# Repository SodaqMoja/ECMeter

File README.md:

ECMeter
=======

This repository includes all open source files related to the EC-Meter
that I have developed for _M2M4ALL_, the company I work for.  This
circuit board includes an analog frontend to measure the electrical
conductivity and temperature of water. The board will have to be cast
in resin with the probes sticking out in order to submerge the board
for long durations.

This is the Arduino library required to use the EC Meter easily. The
hardware files are also included.

##Documentation
We've added Doxygen so that the documentation can be generated from
the source code.

##Examples

#####demo
Reads the onboard temperature sensor, system voltage, resistance,
conductivity and prints the value every two seconds.

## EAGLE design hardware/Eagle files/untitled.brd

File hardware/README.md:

#Hardware

_BOM.xlsx_ includes the build-of-materials for this project including Farnell links. If you are sourcing the components from another website, please make sure the resistors are 1% thin-film or better. The analog circuitry has very fine tolerances.

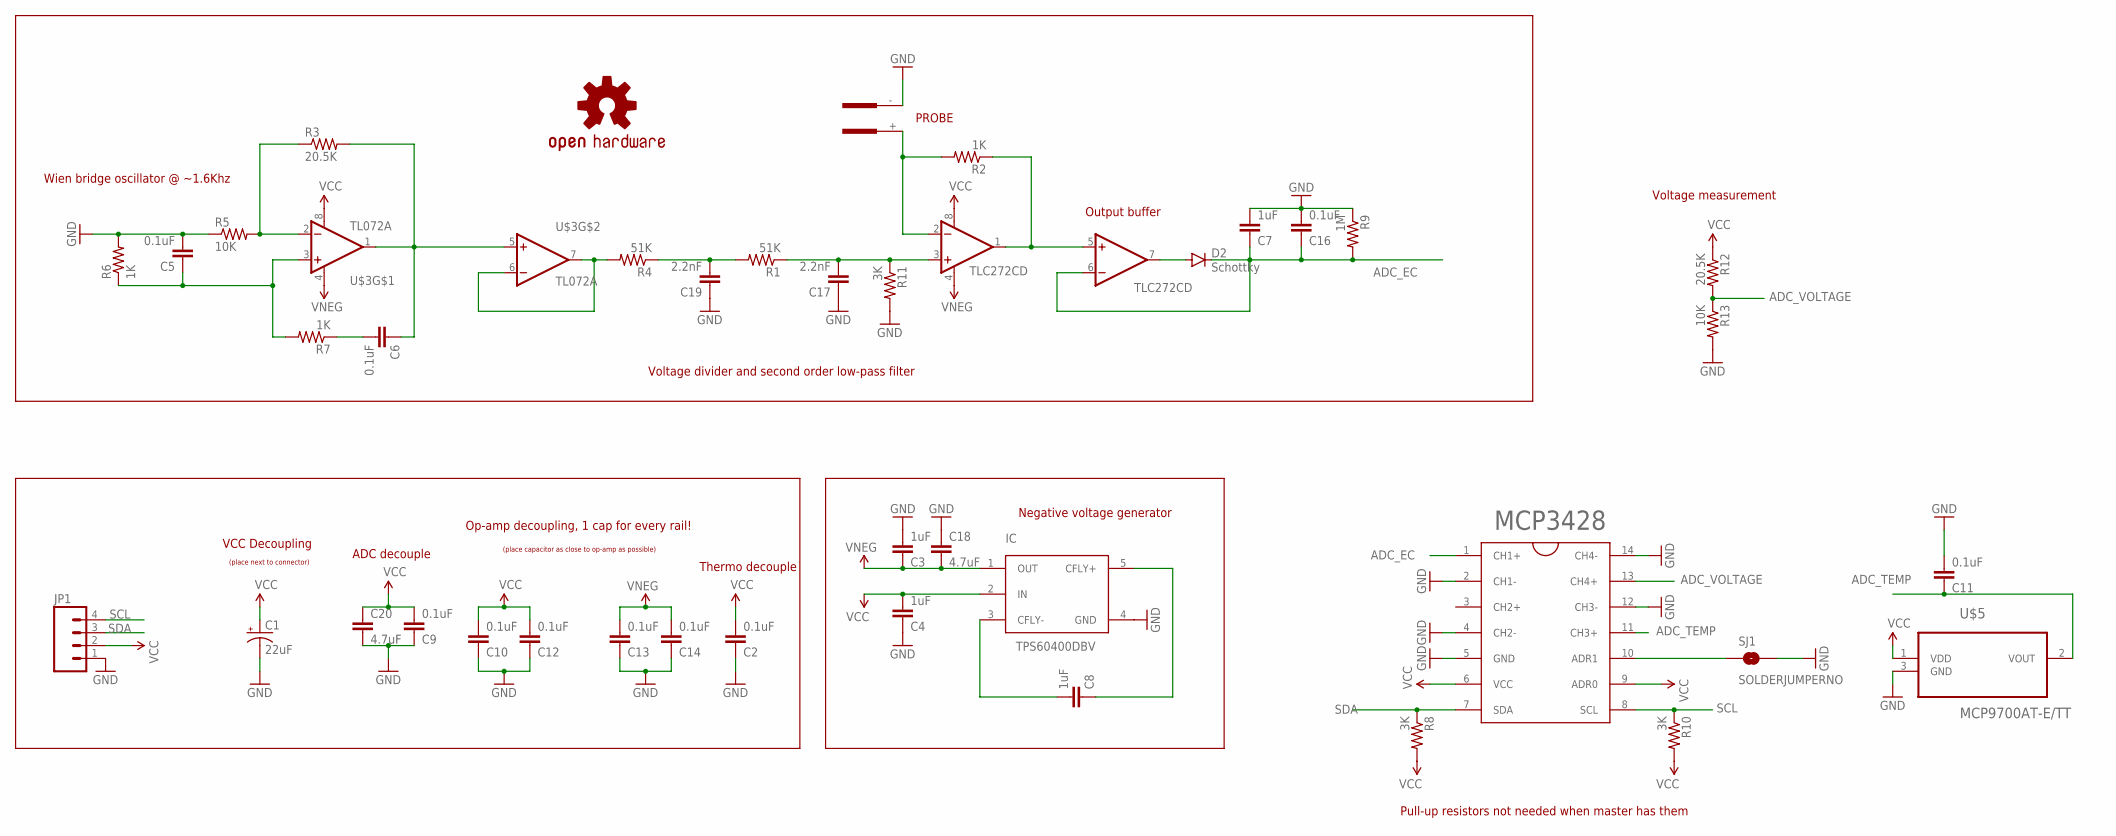
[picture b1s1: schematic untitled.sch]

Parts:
C1: 22uF; EIA3216
C2, C5, C6, C9, C10, C11, C12, C13, C14, C16: 0.1uF; 0603-CAP
C3, C4, C7, C8: 1uF; 0603-CAP
C17, C19: 2.2nF; 0603-CAP
C18, C20: 4.7uF; 0805
D2: Schottky; SOD-323
IC: TPS60400DBV; SOT23-5
JP1: M04LONGPADS; 1X04_LONGPADS
LOGO1: OSHW-LOGOM; OSHW-LOGO-M
MCP3428: MCP3428; SO14
R1, R4: 51K; 0603-RES
R2, R6, R7: 1K; 0603-RES
R3, R12: 20.5K; 0603-RES
R5, R13: 10K; 0603-RES
R8, R10, R11: 3K; 0603-RES
R9: 1M; 0603-RES
SJ1: SOLDERJUMPERNO; SJ_2S-NO
U$1: TLC272CD; SOIC8
U$2: K1-PROBE
U$3: TL072A; SOIC8
U$5: MCP9700AT-E/TT; SOT95P237X112-3N

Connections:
ADC_EC: C7.1, C16.1, D2.C, MCP3428.1 (CH1+), R9.2, U$1.6 (-IN)
ADC_TEMP: C11.1, MCP3428.11 (CH3+), U$5.2 (VOUT)
ADC_VOLTAGE: MCP3428.13 (CH4+), R12.2, R13.1
GND: C1.C (-), C2.1, C3.2, C4.1, C5.2, C7.2, C9.1, C10.1, C11.2, C12.1, C13.1, C14.1, C16.2, C17.1, C18.1, C19.1, C20.2, IC.4 (GND), JP1.1, MCP3428.2 (CH1-), MCP3428.4 (CH2-), MCP3428.5 (GND), MCP3428.12 (CH3-), MCP3428.14 (CH4-), R5.1, R6.2, R9.1, R11.2, R13.2, SJ1.2, U$2.-, U$5.3 (GND)
unnamed: C6.1, R3.2, U$3.1 (OUT), U$3.5 (+IN)
unnamed: R3.1, R5.2, U$3.2 (-IN)
unnamed: C5.1, R6.1, R7.2, U$3.3 (+IN)
unnamed: C6.2, R7.1
unnamed: R4.2, U$3.6 (-IN), U$3.7 (OUT)
unnamed: C17.2, R1.1, R11.1, U$1.3 (+IN)
unnamed: R2.1, U$1.1 (OUT), U$1.5 (+IN)
unnamed: R2.2, U$1.2 (-IN), U$2.+
unnamed: D2.A, U$1.7 (OUT)
unnamed: C8.1, IC.5 (CFLY+)
unnamed: C8.2, IC.3 (CFLY-)
unnamed: C19.2, R1.2, R4.1
unnamed: MCP3428.10 (ADR1), SJ1.1
SCL: JP1.4, MCP3428.8 (SCL), R10.1
SDA: JP1.3, MCP3428.7 (SDA), R8.1
VCC: C1.A (+), C2.2, C4.2, C9.2, C10.2, C12.2, C20.1, IC.2 (IN), JP1.2, MCP3428.6 (VCC), MCP3428.9 (ADR0), R8.2, R10.2, R12.1, U$1.8 (V+), U$3.8 (V+), U$5.1 (VDD)
VNEG: C3.1, C13.2, C14.2, C18.2, IC.1 (OUT), U$1.4 (V-), U$3.4 (V-)

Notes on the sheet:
VCC Decoupling
Wien bridge oscillator @ ~1.6Khz
Output buffer
Op-amp decoupling, 1 cap for every rail!
(place capacitor as close to op-amp as possible)
(place next to connector)
Negative voltage generator
PROBE
ADC decouple
Thermo decouple
Voltage divider and second order low-pass filter
Voltage measurement
Pull-up resistors not needed when master has them

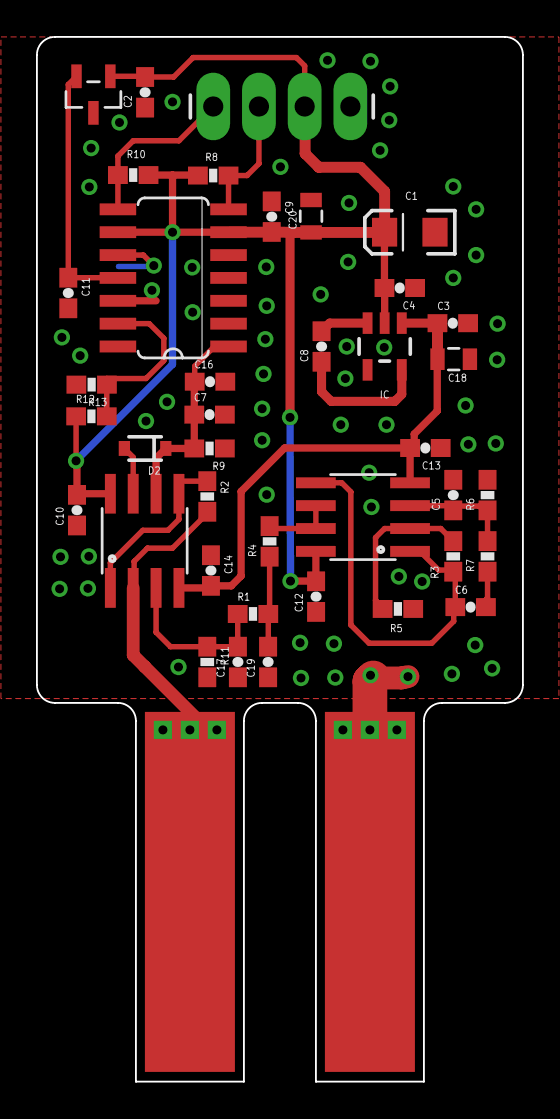
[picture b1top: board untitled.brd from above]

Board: 2 copper layers, 27.0 x 58.0 mm, 42 parts (1 on the bottom side), 21 nets.

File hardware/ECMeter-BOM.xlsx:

Qty | Value | Device | Package | Farnell
10 | 0.1uF | CAPACITOR | 0603 | x
4 | 1uF | CAPACITOR | 0603 | 1759399
3 | 1K | 1% 0603 RESISTOR | 0603 | 2325213
3 | 3K | 1% 0603 RESISTOR | 0603 | 2059357
2 | 10K | 1% 0603 RESISTOR | 0603 | 2325241
2 | 2.2nF | CAPACITOR | 0603 | 1658866
2 | 4.7uF | CAPACITOR | 0805 | 1759420
2 | 51K | 1% 0603 RESISTOR | 0603 | 9331310
1 | 22uF | CAPACITOR | 3216 | 2333013
1 | 1M | 1% 0603 RESISTOR | 0603 | 9330410
2 | 20.5K | 1% 0603 RESISTOR | 0603 | 1527616
1 | MCP3428 | MCP3428 | SO14 | 1825014
1 | MCP9700AT | MCP9700AT-E/TT | SOT23-3 | 1605577
1 | Schottky | DIODESOD | SOD-323 | 1907691
2 | TL072A | TL072A | SOIC8 | 9593322
1 | TPS60400DBV | TPS60400DBV | SOT23-5 | 8457751

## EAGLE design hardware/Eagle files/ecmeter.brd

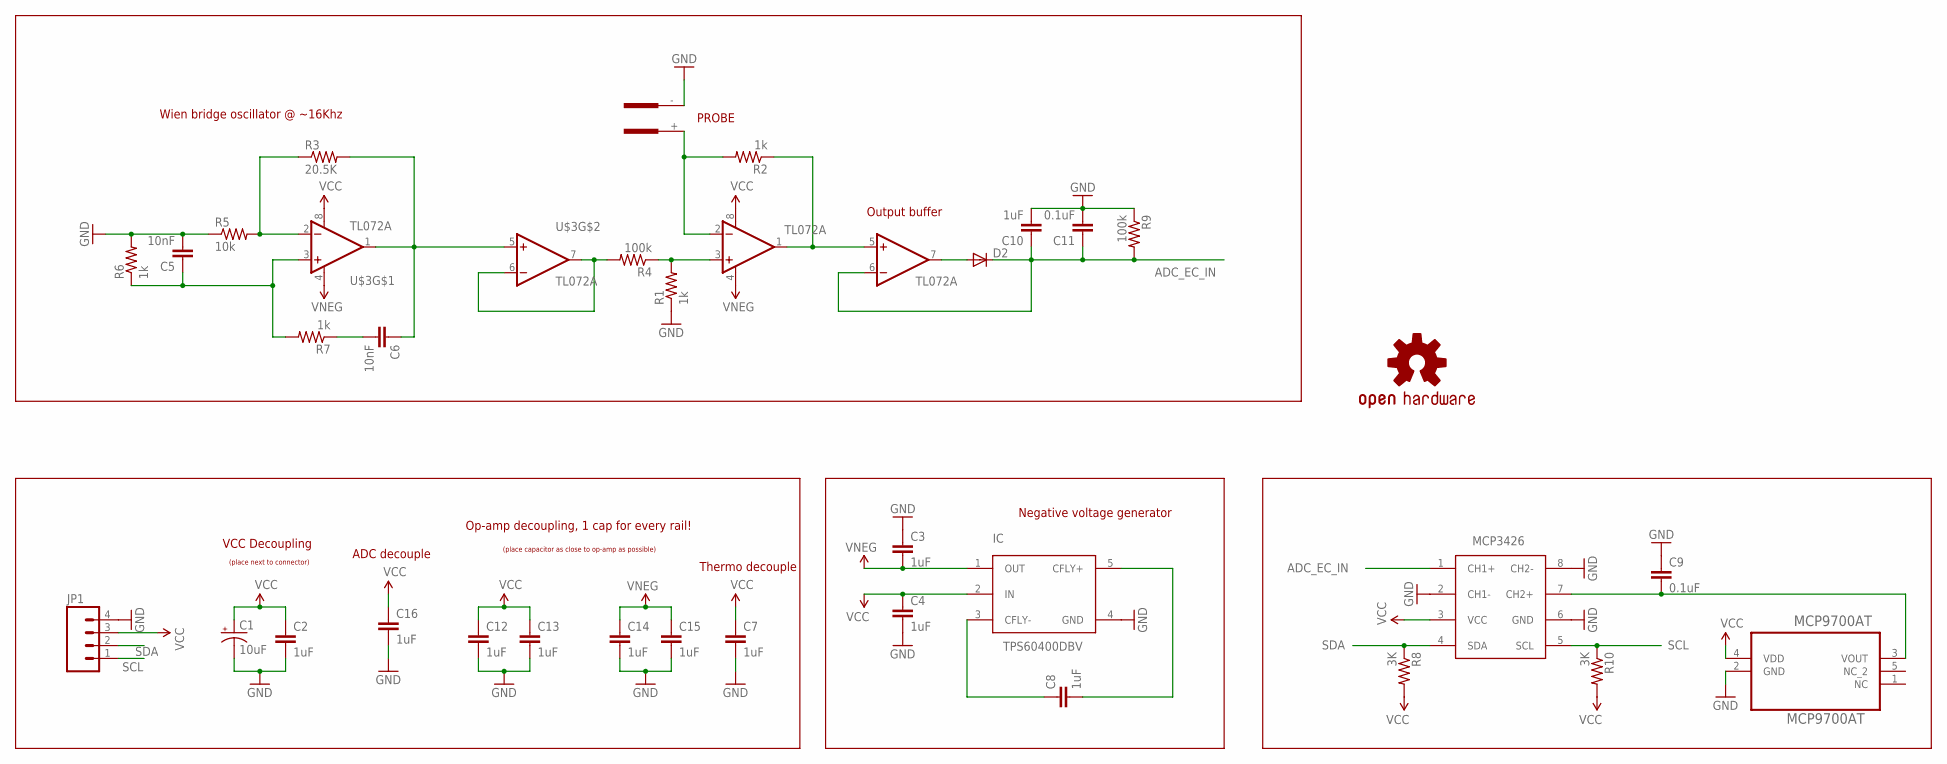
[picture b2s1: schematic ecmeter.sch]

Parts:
C1: 10uF; EIA3216
C2, C3, C4, C7, C8, C10, C12, C13, C14, C15, C16: 1uF; 0805
C5, C6: 10nF; 0603-CAP
C9, C11: 0.1uF; 0805
D2: DIODESOD; SOD-323
IC: TPS60400DBV; SOT23-5
JP1: M04POLAR; MOLEX-1X4
LOGO1: OSHW-LOGOM; OSHW-LOGO-M
MCP9700AT: MCP9700AT; SOT65P210X110-5N
R1, R2, R6, R7: 1k; 0603-RES
R3: 20.5K; 0603-RES
R4, R9: 100k; 0603-RES
R5: 10k; 0603-RES
R8, R10: 3K; 0603-RES
U$1, U$3: TL072A; SOIC8
U$2: K1-PROBE
U$4: MCP3426; SOIC8

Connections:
ADC_EC_IN: C10.1, C11.1, D2.1 (C), R9.2, U$1.6 (-IN), U$4.1 (CH1+)
GND: C1.C (-), C2.2, C3.1, C4.2, C5.2, C7.2, C9.1, C10.2, C11.2, C12.2, C13.2, C14.2, C15.2, C16.2, IC.4 (GND), JP1.4, MCP9700AT.2 (GND), R1.1, R5.1, R6.2, R9.1, U$2.-, U$4.2 (CH1-), U$4.6 (GND), U$4.8 (CH2-)
unnamed: C6.1, R3.2, U$3.1 (OUT), U$3.5 (+IN)
unnamed: R3.1, R5.2, U$3.2 (-IN)
unnamed: C5.1, R6.1, R7.2, U$3.3 (+IN)
unnamed: C6.2, R7.1
unnamed: R4.2, U$3.6 (-IN), U$3.7 (OUT)
unnamed: R1.2, R4.1, U$1.3 (+IN)
unnamed: R2.1, U$1.1 (OUT), U$1.5 (+IN)
unnamed: R2.2, U$1.2 (-IN), U$2.+
unnamed: D2.2 (A), U$1.7 (OUT)
unnamed: C8.2, IC.5 (CFLY+)
unnamed: C8.1, IC.3 (CFLY-)
unnamed: C9.2, MCP9700AT.3 (VOUT), U$4.7 (CH2+)
SCL: JP1.1, R10.1, U$4.5 (SCL)
SDA: JP1.2, R8.1, U$4.4 (SDA)
VCC: C1.A (+), C2.1, C4.1, C7.1, C12.1, C13.1, C16.1, IC.2 (IN), JP1.3, MCP9700AT.4 (VDD), R8.2, R10.2, U$1.8 (V+), U$3.8 (V+), U$4.3 (VCC)
VNEG: C3.2, C14.1, C15.1, IC.1 (OUT), U$1.4 (V-), U$3.4 (V-)

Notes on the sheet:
VCC Decoupling
Wien bridge oscillator @ ~16Khz
Output buffer
Op-amp decoupling, 1 cap for every rail!
(place capacitor as close to op-amp as possible)
(place next to connector)
Negative voltage generator
PROBE
ADC decouple
Thermo decouple

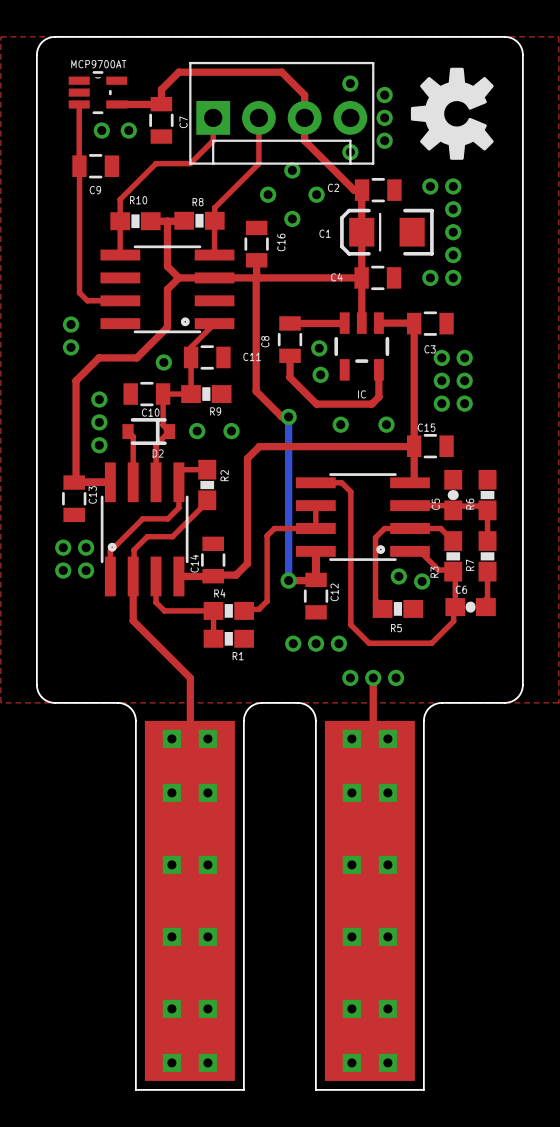
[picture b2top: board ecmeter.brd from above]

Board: 2 copper layers, 27.0 x 58.5 mm, 35 parts (0 on the bottom side), 18 nets.

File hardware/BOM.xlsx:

Qty | Qty * 10 | Value | Device | Package | Farnell |  | Legend:
1 | 10 | Schottky | DIODESOD | SOD-323 | 1907691 |  | SILICON
2 | 20 | 100k | RESISTOR | 0603-RES | 1527690 |  | RESISTOR
1 | 10 | 10k | RESISTOR | 0603-RES | 1527581 |  | IC
1 | 10 | 10uF | TANTALUM CAP | EIA3216 | 2333009 |  | CAPACITOR
1 | 10 | 20.5K | RESISTOR | 0603-RES | 1527616
1 | 10 | MCP3426 | MCP3426 ADC | SOIC8 | 1825012
1 | 10 | MCP9700AT | MCP9700AT | SC70 | 1332165
1 | 10 | TPS60400DBV | TPS60400DBV | SOT23-5 | 8457751
2 | 20 | 0.1uF | CAPACITOR | 0805 | 1759166
2 | 20 | 10nF | CAPACITOR | 0603-CAP | 1865545
2 | 20 | 3K | RESISTOR | 0603-RES | 2326512
2 | 20 | TL072A | TL072A | SOIC8 | 9593322
4 | 40 | 1k | RESISTOR | 0603-RES | 2008335
11 | 110 | 1uF | CAPACITOR | 0805 | 9227792

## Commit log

2014-05-25 Added library folder, testing
2014-05-25 Added example to libraries folder
2014-05-26 Added hardware files
2014-09-05 Updates library and added example sketch
2014-10-10 Updated library
    Added way to measure resistance and conductivity
2014-10-24 Reorganize directory structure
2014-10-24 Updated to revision 2
    All files updated to revision 2 of the ECMeter. New code and hardware
    files added.
2014-10-24 Remove reference to SoftI2CMaster in the README
    Also updated the README about the example(s)
2014-11-01 Added conductivity measurement
    Added (calibrated) conductivity measurement. Also added 2 lines of code
    that will reduce the I2C clock speed so long range communication is
    possible.
2014-11-01 Move EC_ADDR macro to ECMeter.cpp
    And also the Wire.h include is moved to ECMeter.cpp
2014-11-07 Testing SourceTree
2014-11-07 Removed text files from sourcetree test
2014-11-07 Create a class ECMeter and all functions class methods
2014-11-07 Make calibrationVal a private constant for ECMeter
2014-11-11 Move all macros (defines) to the .cpp module and make readChannel private
    The header file is now as clean as can be. This is the class interface.
    Nothing more must be accessible for the outside world.
2014-11-11 The channel values are (16 bit) signed
2014-11-11 Split readChannel into a function that reads raw and one that does voltage
2014-11-14 Removed hardware folder, will be added later to a dedicated hardware repository.
2014-11-17 Added <inttypes.h>
2014-11-17 Changed I2C clock speed to 10Khz
2014-11-22 Only white space changes (indent 2, no TAB's)
    We're using indent 2, which is more or less standard for Arduino. Also
    I don't like the use of TAB, unless they represent 8 spaces.
2014-11-22 Use stdint.h instead of inttypes.h because we only need the types
    inttypes.h (despite the name) is used to give all the printf format stuff
    and we don't need that.
2014-11-22 Add .gitignore
2014-11-22 Add first set of doxygen comments
2014-11-22 Add LGPL
2014-11-22 More comments converted to doxygen style
2014-11-23 Replace the delay by a while loop waiting for the ADC to complete
    Notice that this code is not "watchdog" safe. If the device never completes
    the ADC it will hang forever.
2014-11-23 Replace hardcoded constant with a formula to compute the TWBR value
2014-11-23 A few changes in comment
2014-11-29 Add a timeout to readChannel, it returns 0x8000 when it times out

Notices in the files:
parts and their libraries:
SparkFun-Connectors: Licensing: CC v3.0 Share-Alike You are welcome to use this library for commercial purposes.
SparkFun-Retired: Licensing:Creative Commons ShareAlike 4.0 International - https://creativecommons.org/licenses/by-sa/4.0
